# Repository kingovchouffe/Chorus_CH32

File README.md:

# Chorus_CH32
 Chorus effect based on ch32v003

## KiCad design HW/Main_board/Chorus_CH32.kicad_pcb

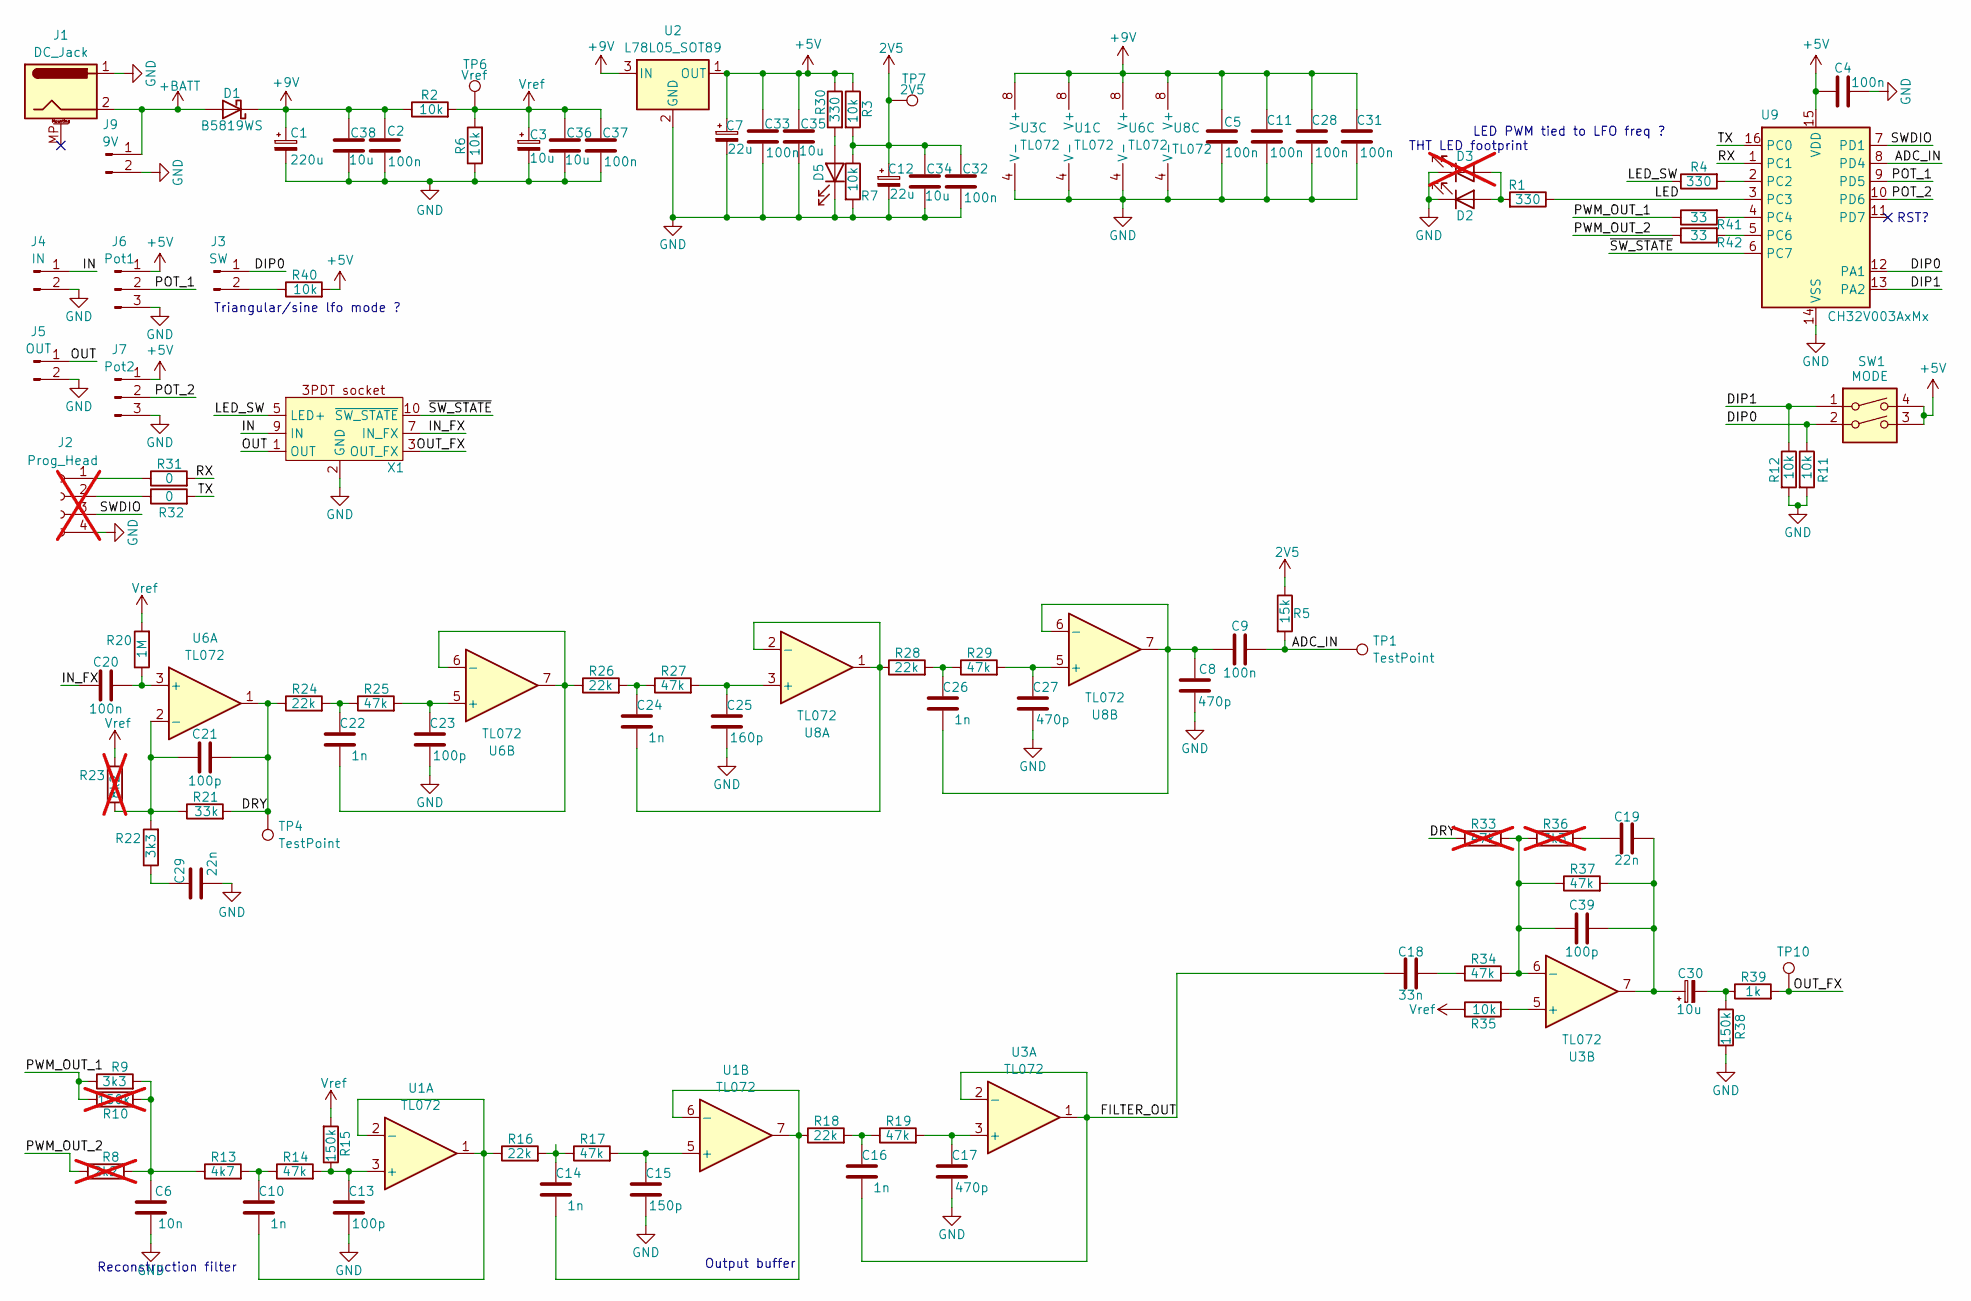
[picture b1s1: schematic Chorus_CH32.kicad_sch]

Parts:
C1: 220u; CP_Elec_6.3x7.7
C2, C4, C5, C9, C11, C20, C28, C31, C32, C33, C37: 100n; C_0603_1608Metric
C3: 10u; CP_Elec_5x5.4; lcsc C7171
C6: 10n; C_0603_1608Metric
C7, C12: 22u; CP_Elec_5x5.4; lcsc C7171
C8, C17, C27: 470p; C_0603_1608Metric
C10, C14, C16, C22, C24, C26: 1n; C_0603_1608Metric
C13, C21, C23, C39: 100p; C_0603_1608Metric
C15: 150p; C_0603_1608Metric
C18: 33n; C_0603_1608Metric
C19, C29: 22n; C_0603_1608Metric
C25: 160p; C_0603_1608Metric
C30: 10u; CP_Elec_5x5.4
C34, C35, C36, C38: 10u; C_0603_1608Metric
D1: B5819WS; D_SOD-323
D2, D5: CTL1; LED_0603_1608Metric
D3: CTL1; PinSocket_1x02_P1.27mm_Vertical; not fitted
J1: DC_Jack; BarrelJack_Horizontal
J2: Prog_Head; PinHeader_1x04_P1.27mm_Vertical; not fitted
J3: SW; PinHeader_1x02_P1.27mm_Vertical
J4: IN; PinHeader_1x02_P1.27mm_Vertical
J5: OUT; PinHeader_1x02_P1.27mm_Vertical
J6: Pot1; PinHeader_1x03_P1.27mm_Vertical
J7: Pot2; PinHeader_1x03_P1.27mm_Vertical
J9: 9V; PinHeader_1x02_P1.27mm_Vertical
R1, R4, R30: 330; R_0603_1608Metric
R2, R3, R6, R7, R11, R12, R35, R40: 10k; R_0603_1608Metric
R5: 15k; R_0603_1608Metric
R8: 2k2; R_0603_1608Metric; not fitted
R9, R22: 3k3; R_0603_1608Metric
R10: 150k; R_0603_1608Metric; not fitted
R13: 4k7; R_0603_1608Metric
R14, R17, R19, R25, R27, R29, R34, R37: 47k; R_0603_1608Metric
R15, R38: 150k; R_0603_1608Metric
R16, R18, R24, R26, R28: 22k; R_0603_1608Metric
R20: 1M; R_0603_1608Metric
R21: 33k; R_0603_1608Metric
R23: 8k2; R_0603_1608Metric; not fitted
R31, R32: 0; R_0603_1608Metric
R33: 47k; R_0603_1608Metric; not fitted
R36: 3k3; R_0603_1608Metric; not fitted
R39: 1k; R_0603_1608Metric
R41, R42: 33; R_0603_1608Metric
SW1: MODE; SW_DIP_SPSTx02_Slide_KingTek_DSHP02TS_W7.62mm_P1.27mm
TP1, TP4, TP10: TestPoint; TestPoint_Pad_D1.0mm
TP6: Vref; TestPoint_Pad_D1.0mm
TP7: 2V5; TestPoint_Pad_D1.0mm
U1, U3, U6, U8: TL072; SOIC-8_3.9x4.9mm_P1.27mm
U2: L78L05_SOT89; SOT-89-3
U9: CH32V003AxMx; SOP-16_3.9x9.9mm_P1.27mm
X1: PinHeader_1x10_P1.27mm_Vertical

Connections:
2V5: C12.1, C32.1, C34.1, R3.2, R5.1, R7.1, TP7.1
+5V: C4.1, C7.1, C33.1, C35.1, J6.1, J7.1, R3.1, R30.1, R40.2, SW1.3, SW1.4, U2.1 (OUT), U9.15 (VDD); also elsewhere on the board
+9V: C1.1, C2.1, C5.1, C11.1, C28.1, C31.1, C38.1, D1.1 (K), R2.1, U1.8 (V+), U2.3 (IN), U3.8 (V+), U6.8 (V+), U8.8 (V+)
+BATT: D1.2 (A), J1.2, J9.1
/ADC_IN: C9.2, R5.2, TP1.1, U9.8 (PD4)
/DIP0: J3.1, R11.1, SW1.2, U9.12 (PA1); also elsewhere on the board
/DIP1: R12.1, SW1.1, U9.13 (PA2); also elsewhere on the board
/DRY: C21.2, R21.2, R24.1, R33.1, TP4.1, U6.1
/FILTER_OUT: C16.2, C18.1, U3.1, U3.2 (-)
/IN: J4.1, X1.9 (IN)
/IN_FX: C20.1, X1.7 (IN_FX)
/LED: R1.1, U9.3 (PC3)
/LED_SW: R4.1, X1.5 (LED+)
/OUT: J5.1, X1.1 (OUT)
/OUT_FX: R39.2, TP10.1, X1.3 (OUT_FX)
/POT_1: J6.2, U9.9 (PD5); also elsewhere on the board
/POT_2: J7.2, U9.10 (PD6); also elsewhere on the board
/PWM_OUT_1: R9.1, R10.1, R41.1
/PWM_OUT_2: R8.1, R42.1
/RX: R31.2, U9.1 (PC1)
/SWDIO: J2.3, U9.7 (PD1); also elsewhere on the board
/TX: R32.2, U9.16 (PC0)
/~SW_STATE: U9.6 (PC7), X1.10 (~SW_STATE)
GND: C1.2, C2.2, C3.2, C4.2, C5.2, C6.2, C7.2, C8.2, C11.2, C12.2, C13.2, C15.2, C17.2, C23.2, C25.2, C27.2, C28.2, C29.2, C31.2, C32.2, C33.2, C34.2, C35.2, C36.2, C37.2, C38.2, D2.1 (K), D3.1 (K), D5.1 (K), J1.1, J2.4, J4.2, J5.2, J6.3, J7.3, J9.2, R6.1, R7.2, R11.2, R12.2, R38.1, U1.4 (V-), U2.2 (GND), U3.4 (V-), U6.4 (V-), U8.4 (V-), U9.14 (VSS), X1.2 (GND), X1.4 (GND), X1.6 (GND), X1.8 (GND); also elsewhere on the board
unnamed: C6.1, R8.2, R9.2, R10.2, R13.1
unnamed: C10.1, R13.2, R14.1
unnamed: C14.1, R16.2, R17.1
unnamed: C16.1, R18.2, R19.1
unnamed: C18.2, R34.1
unnamed: C19.1, R36.2
unnamed: C19.2, C30.1, C39.2, R37.2, U3.7
unnamed: C22.1, R24.2, R25.1
unnamed: C24.1, R26.2, R27.1
unnamed: C26.1, R28.2, R29.1
unnamed: C29.1, R22.1
unnamed: C30.2, R38.2, R39.1
unnamed: D2.2 (A), D3.2 (A), R1.2
unnamed: D5.2 (A), R30.2
unnamed 38: J2.1, R31.1; also elsewhere on the board
unnamed 39: J2.2, R32.1; also elsewhere on the board
unnamed: J3.2, R40.1
unnamed: C13.1, R14.2, R15.1, U1.3 (+)
unnamed: C10.2, R16.1, U1.1, U1.2 (-)
unnamed: C15.1, R17.2, U1.5 (+)
unnamed: C14.2, R18.1, U1.6 (-), U1.7
unnamed: C17.1, R19.2, U3.3 (+)
unnamed: R35.2, U3.5 (+)
unnamed: C39.1, R33.2, R34.2, R36.1, R37.1, U3.6 (-)
unnamed: C20.2, R20.1, U6.3 (+)
unnamed: C21.1, R21.1, R22.2, R23.1, U6.2 (-)
unnamed: C23.1, R25.2, U6.5 (+)
unnamed: C22.2, R26.1, U6.6 (-), U6.7
unnamed: C25.1, R27.2, U8.3 (+)
unnamed: C24.2, R28.1, U8.1, U8.2 (-)
unnamed: C27.1, R29.2, U8.5 (+)
unnamed: C8.1, C9.1, C26.2, U8.6 (-), U8.7
unnamed: R4.2, U9.2 (PC2)
unnamed: R41.2, U9.4 (PC4)
unnamed: R42.2, U9.5 (PC6)
Vref: C3.1, C36.1, C37.1, R2.2, R6.2, R15.2, R20.2, R23.2, R35.1, TP6.1

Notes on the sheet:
LED PWM tied to LFO freq ?
THT LED footprint
Triangular/sine lfo mode ?
RST?
Reconstruction filter
Output buffer

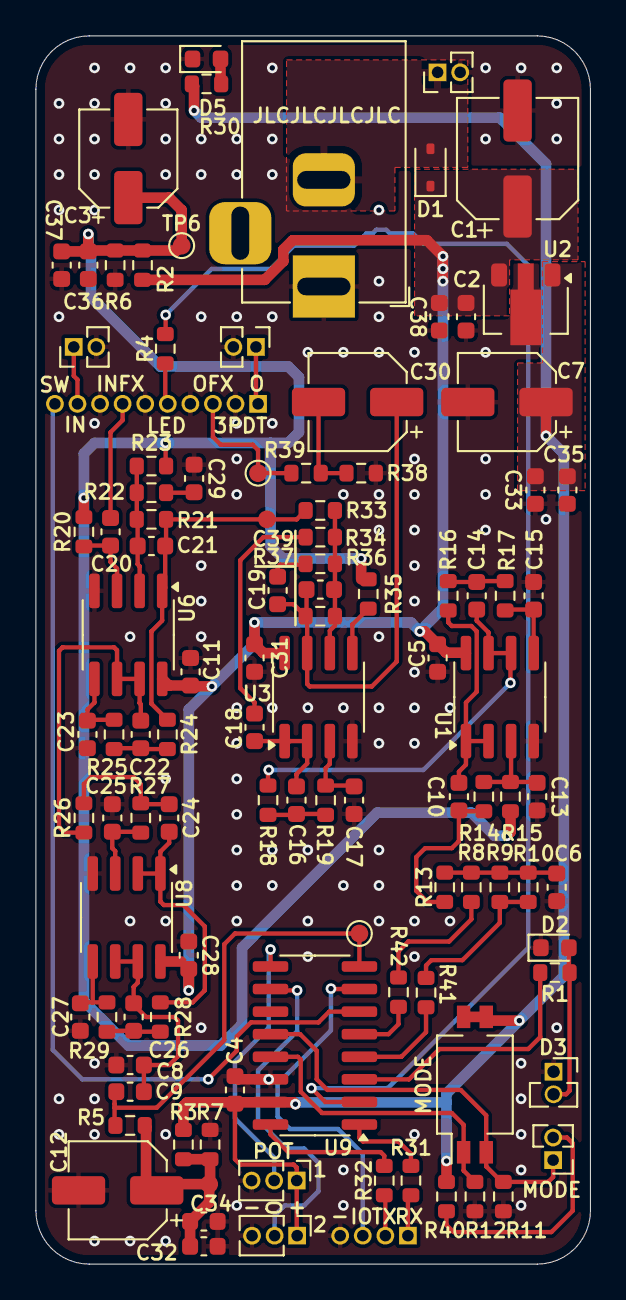
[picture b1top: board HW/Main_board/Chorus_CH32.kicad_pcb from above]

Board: 2 copper layers, 31.2 x 69.1 mm, 106 parts (0 on the bottom side), 60 nets.

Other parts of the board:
DEBUG: Prog_Head; PinHeader_1x04_P1.27mm_Vertical
MODE: MODE; SW_DIP_SPSTx02_Slide_KingTek_DSHP02TS_W7.62mm_P1.27mm
POT: Pot1; PinHeader_1x03_P1.27mm_Vertical
POT2: Pot2; PinHeader_1x03_P1.27mm_Vertical

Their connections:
+5V: MODE.3, MODE.4, POT.1, POT2.1; also elsewhere on the board
/DIP0: MODE.2; also elsewhere on the board
/DIP1: MODE.1; also elsewhere on the board
/POT_1: POT.2; also elsewhere on the board
/POT_2: POT2.2; also elsewhere on the board
/SWDIO: DEBUG.3; also elsewhere on the board
GND: DEBUG.4, POT.3, POT2.3; also elsewhere on the board
unnamed 38: DEBUG.1; also elsewhere on the board
unnamed 39: DEBUG.2; also elsewhere on the board

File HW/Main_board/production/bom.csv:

Designator,Footprint,Quantity,Value,LCSC Part #
C1,CP_Elec_6.3x7.7,1,220u,
"C10, C14, C16, C22, C24, C26",0603,6,1n,
"C11, C2, C20, C28, C31, C32, C33, C37, C4, C5, C9",0603,11,100n,
"C12, C7",CP_Elec_5x5.4,2,22u,
"C13, C21, C23, C39",0603,4,100p,
C15,0603,1,150p,
"C17, C27, C8",0603,3,470p,
C18,0603,1,33n,
"C19, C29",0603,2,22n,
C25,0603,1,160p,
"C3, C30",CP_Elec_5x5.4,2,10u,
"C34, C35, C36, C38",0603,4,10u,
C6,0603,1,10n,
D1,D_SOD-323,1,B5819WS,
"D2, D5",0603,2,CTL1,
J1,BarrelJack_Horizontal,1,DC_Jack,
J3,PinHeader_1x02_P1.27mm_Vertical,1,SW,
J4,PinHeader_1x02_P1.27mm_Vertical,1,IN,
J5,PinHeader_1x02_P1.27mm_Vertical,1,OUT,
J9,PinHeader_1x02_P1.27mm_Vertical,1,9V,
MODE,SW_DIP_SPSTx02_Slide_KingTek_DSHP02TS_W7.62mm_P1.27mm,1,MODE,
POT,PinHeader_1x03_P1.27mm_Vertical,1,Pot1,
POT2,PinHeader_1x03_P1.27mm_Vertical,1,Pot2,
"R1, R30, R4",0603,3,330,
"R11, R12, R2, R3, R35, R40, R6, R7",0603,8,10k,
R13,0603,1,4k7,
"R14, R17, R19, R25, R27, R29, R34, R37",0603,8,47k,
"R15, R38",0603,2,150k,
"R16, R18, R24, R26, R28",0603,5,22k,
R20,0603,1,1M,
R21,0603,1,33k,
"R22, R9",0603,2,3k3,
"R31, R32",0603,2,0,
R39,0603,1,1k,
"R41, R42",0603,2,33,
R5,0603,1,15k,
"TP1, TP10, TP4",TestPoint_Pad_D1.0mm,3,TestPoint,
TP6,TestPoint_Pad_D1.0mm,1,Vref,
TP7,TestPoint_Pad_D1.0mm,1,2V5,
"U1, U3, U6, U8",SOIC-8_3.9x4.9mm_P1.27mm,4,TL072,
U2,SOT-89-3,1,L78L05_SOT89,
U9,SOP-16_3.9x9.9mm_P1.27mm,1,CH32V003AxMx,
X1,PinHeader_1x10_P1.27mm_Vertical,1,~,

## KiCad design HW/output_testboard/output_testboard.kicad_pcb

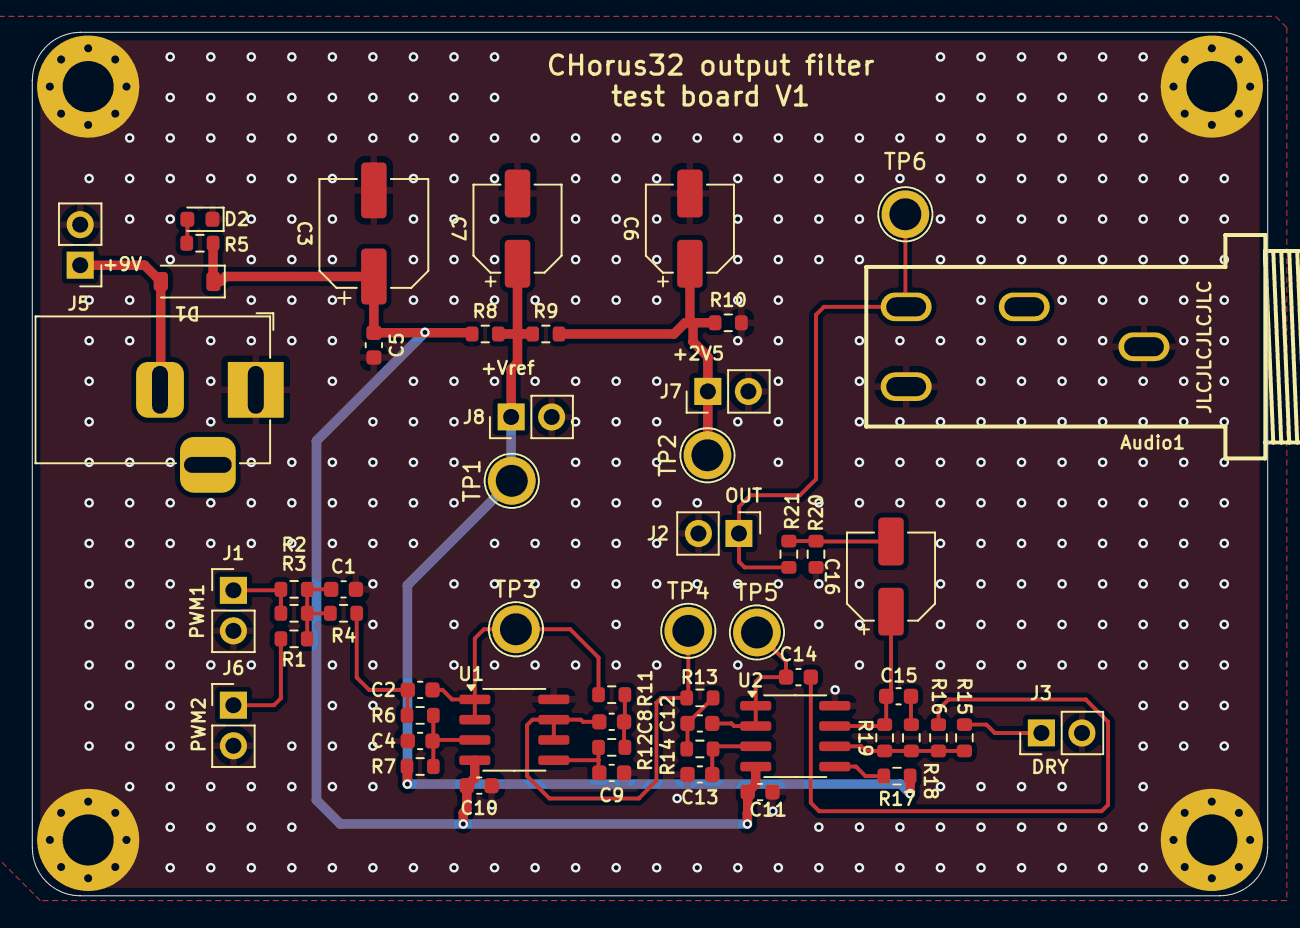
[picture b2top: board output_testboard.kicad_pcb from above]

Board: 2 copper layers, 77.4 x 54.1 mm, 60 parts (0 on the bottom side), 26 nets.

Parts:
Audio1: PJ-603A; AUDIO-TH_PJ-603A_1
C1: 15n; C_0603_1608Metric
C2, C8, C12: 1n; C_0603_1608Metric
C3: 100u; CP_Elec_6.3x7.7
C4: 100p; C_0603_1608Metric
C5, C10, C11: 100n; C_0603_1608Metric
C6, C7, C16: 10u; CP_Elec_5x5.4
C9: 160p; C_0603_1608Metric
C13: 470p; C_0603_1608Metric
C14: 33n; C_0603_1608Metric
C15: 22n; C_0603_1608Metric
D1: B5819WS; D_SOD-123
D2: LED; LED_0603_1608Metric
H1, H2, H3, H4: MountingHole_Pad; MountingHole_3.2mm_M3_Pad_Via
J1: IN1; PinHeader_1x02_P2.54mm_Vertical
J2, J3: OUT; PinHeader_1x02_P2.54mm_Vertical
J4: DC_Jack; BarrelJack_Horizontal
J5: 9V; PinHeader_1x02_P2.54mm_Vertical
J6: IN2; PinHeader_1x02_P2.54mm_Vertical
J7: 2V5; PinHeader_1x02_P2.54mm_Vertical
J8: Vref; PinHeader_1x02_P2.54mm_Vertical
R1: 2k2; R_0603_1608Metric
R2: 2M2; R_0603_1608Metric
R3, R7, R20: 150k; R_0603_1608Metric
R4: 4k7; R_0603_1608Metric
R5, R9, R17: 10k; R_0603_1608Metric
R6, R12, R14, R15, R16: 47k; R_0603_1608Metric
R8: 27k; R_0603_1608Metric
R10: 15k; R_0603_1608Metric
R11, R13: 22k; R_0603_1608Metric
R18: 3k3; R_0603_1608Metric
R19: 6k8; R_0603_1608Metric
R21: 1k; R_0603_1608Metric
TP1, TP2, TP3, TP4, TP5, TP6: TestPoint; TestPoint_Plated_Hole_D2.0mm
U1, U2: TL072; SOIC-8_3.9x4.9mm_P1.27mm

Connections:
2V5: C6.1, J7.1, R9.2, R10.1, TP2.1
+9V: C3.1, C5.1, C10.1, C11.1, D1.1 (K), R5.1, R8.1, U1.4 (V-), U2.4 (V-)
+BATT: D1.2 (A), J4.2, J5.1
/DRY: J3.1, R15.1
/FILTER_OUT: C12.2, C14.1, TP5.1, U2.1, U2.2 (-)
/OUT: Audio1.4, J2.1, R21.2, TP6.1
/PWM1_IN: J1.1, R2.1, R3.1
/PWM2_IN: J6.1, R1.1
GND: Audio1.2, Audio1.5, C1.2, C3.2, C4.2, C5.2, C6.2, C7.2, C9.2, C10.2, C11.2, C13.2, D2.1 (K), H1.1, H2.1, H3.1, H4.1, J1.2, J2.2, J3.2, J4.1, J5.2, J6.2, J7.2, J8.2, R10.2, R20.1, U1.8 (V+), U2.8 (V+)
unnamed: C1.1, R1.2, R2.2, R3.2, R4.1
unnamed: C2.1, R4.2, R6.1
unnamed: C8.1, R11.2, R12.1
unnamed: C12.1, R13.2, R14.1
unnamed: C14.2, R16.1
unnamed: C15.1, R18.2
unnamed: C15.2, C16.1, R19.2, U2.7
unnamed: C16.2, R20.2, R21.1
unnamed: D2.2 (A), R5.2
unnamed: C4.1, R6.2, R7.1, U1.3 (+)
unnamed: C2.2, R11.1, TP3.1, U1.1, U1.2 (-)
unnamed: C9.1, R12.2, U1.5 (+)
unnamed: C8.2, R13.1, TP4.1, U1.6 (-), U1.7
unnamed: C13.1, R14.2, U2.3 (+)
unnamed: R17.2, U2.5 (+)
unnamed: R15.2, R16.2, R18.1, R19.1, U2.6 (-)
Vref: C7.1, J8.1, R7.2, R8.2, R9.1, R17.1, TP1.1

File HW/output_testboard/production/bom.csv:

Designator,Footprint,Quantity,Value,LCSC Part #
Audio1,AUDIO-TH_PJ-603A_1,1,PJ-603A,C309273
C1,0603,1,15n,
"C10, C11, C5",0603,3,100n,
"C12, C2, C8",0603,3,1n,
C13,0603,1,470p,
C14,0603,1,33n,
C15,0603,1,22n,
C16,CP_Elec_5x5.4,1,10u,
C4,0603,1,100p,
C9,0603,1,160p,
D1,D_SOD-123,1,B5819WS,
D2,0603,1,LED,
J1,PinHeader_1x02_P2.54mm_Vertical,1,IN1,
"J2, J3",PinHeader_1x02_P2.54mm_Vertical,2,OUT,
J4,BarrelJack_Horizontal,1,DC_Jack,
J5,PinHeader_1x02_P2.54mm_Vertical,1,9V,
J6,PinHeader_1x02_P2.54mm_Vertical,1,IN2,
J7,PinHeader_1x02_P2.54mm_Vertical,1,2V5,
J8,PinHeader_1x02_P2.54mm_Vertical,1,Vref,
"R11, R13",0603,2,22k,
"R12, R14, R16, R6",0603,4,47k,
"R17, R5",0603,2,10k,
R18,0603,1,3k3,
R19,0603,1,6k8,
R2,0603,1,2M2,
"R20, R3, R7",0603,3,150k,
R21,0603,1,1k,
R4,0603,1,4k7,
"TP1, TP2, TP3, TP4, TP5, TP6",TestPoint_Plated_Hole_D2.0mm,6,TestPoint,
"U1, U2",SOIC-8_3.9x4.9mm_P1.27mm,2,TL072,

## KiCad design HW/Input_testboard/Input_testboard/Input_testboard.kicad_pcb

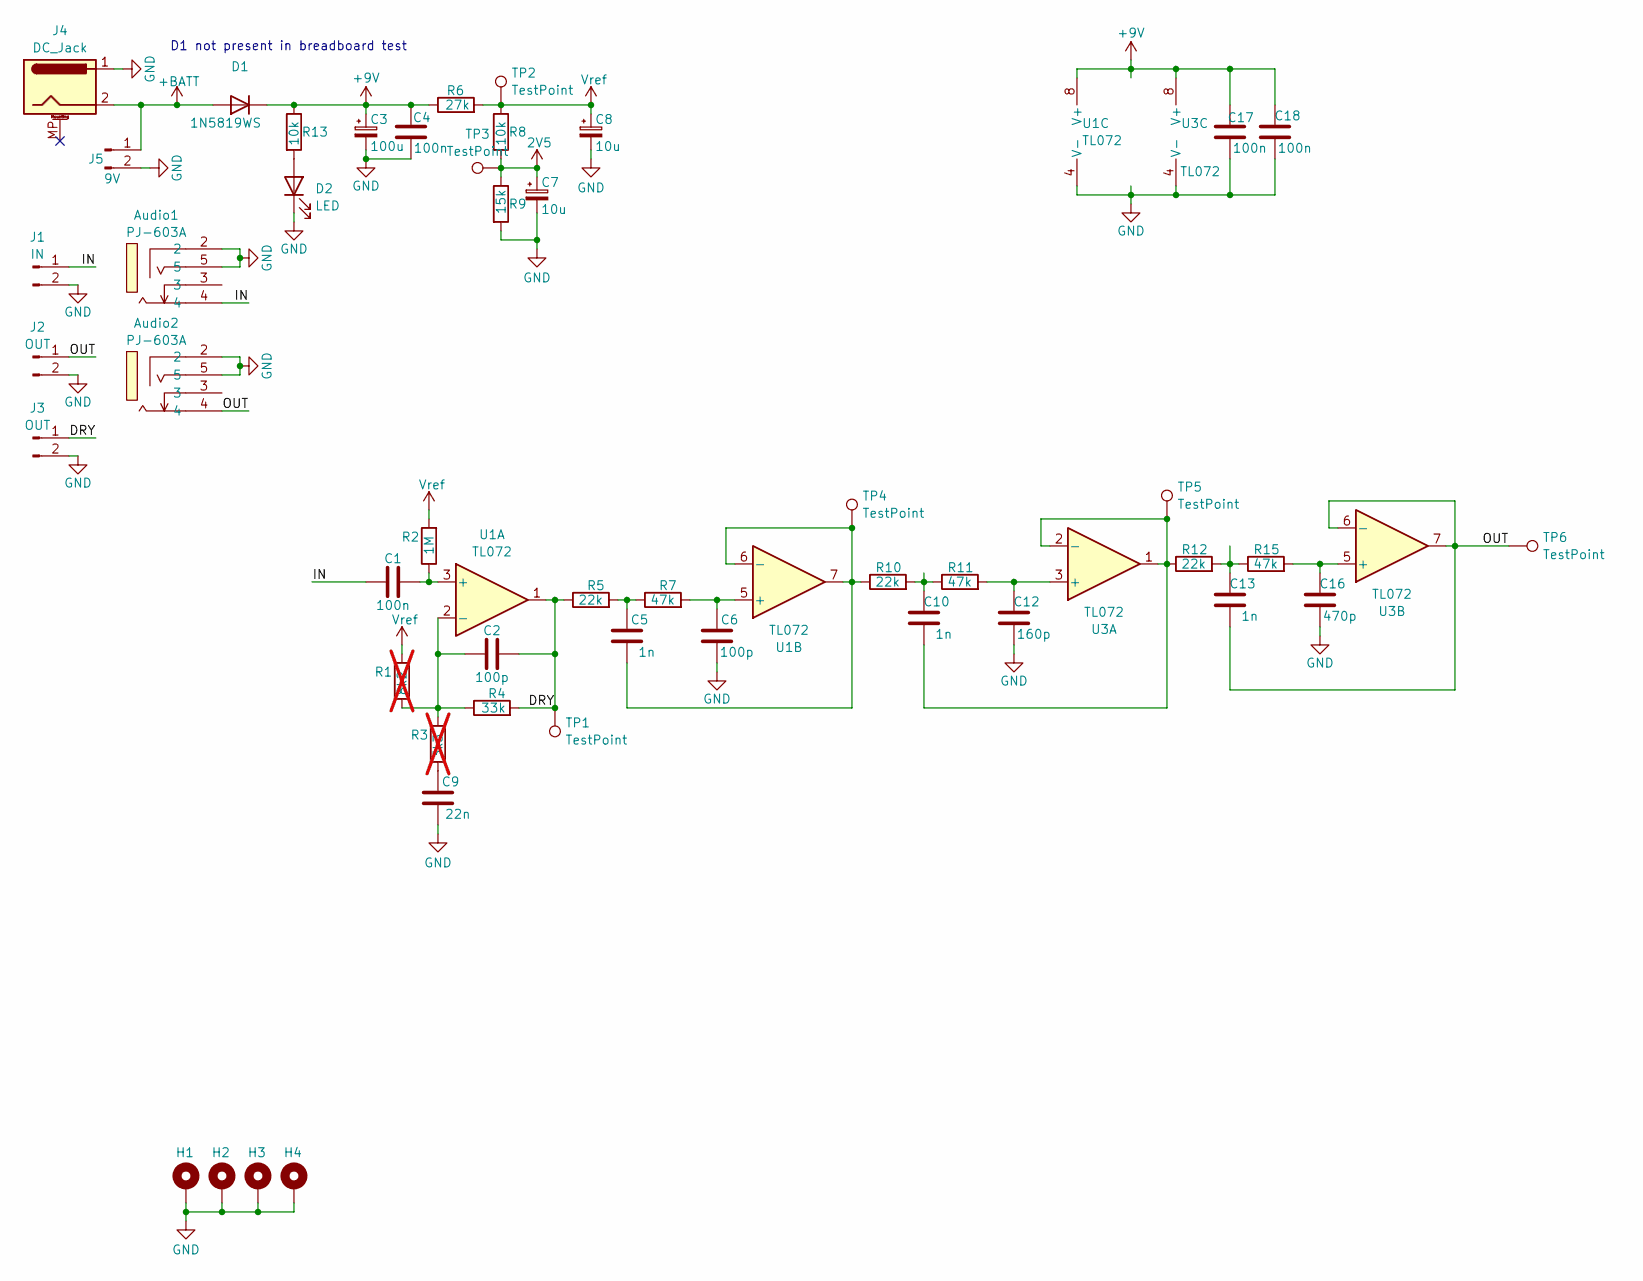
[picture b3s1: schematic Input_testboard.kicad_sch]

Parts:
Audio1, Audio2: PJ-603A; AUDIO-TH_PJ-603A_1; LCSC Part C309273
C1, C4, C17, C18: 100n; C_0603_1608Metric
C2, C6: 100p; C_0603_1608Metric
C3: 100u; CP_Elec_6.3x7.7
C5, C10, C13: 1n; C_0603_1608Metric
C7, C8: 10u; CP_Elec_5x5.4
C9: 22n; C_0603_1608Metric
C12: 160p; C_0603_1608Metric
C16: 470p; C_0603_1608Metric
D1: 1N5819WS; D_SOD-323
D2: LED; LED_0603_1608Metric
H1, H2, H3, H4: MountingHole_3.2mm_M3_Pad_Via
J1: IN; JST_PH_B2B-PH-K_1x02_P2.00mm_Vertical
J2, J3: OUT; JST_PH_B2B-PH-K_1x02_P2.00mm_Vertical
J4: DC_Jack; BarrelJack_Horizontal
J5: 9V; JST_PH_B2B-PH-K_1x02_P2.00mm_Vertical
R1: 8k2; R_0603_1608Metric; not fitted
R2: 1M; R_0603_1608Metric
R3: 3k3; R_0603_1608Metric; not fitted
R4: 33k; R_0603_1608Metric
R5, R10, R12: 22k; R_0603_1608Metric
R6: 27k; R_0603_1608Metric
R7, R11, R15: 47k; R_0603_1608Metric
R8, R13: 10k; R_0603_1608Metric
R9: 15k; R_0603_1608Metric
TP1, TP2, TP3, TP4, TP5, TP6: TestPoint; TestPoint_Pad_D1.0mm
U1, U3: TL072; SOIC-8_3.9x4.9mm_P1.27mm

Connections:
2V5: C7.1, R8.2, R9.1, TP3.1
+9V: C3.1, C4.1, C17.1, C18.1, D1.1 (K), R6.1, R13.1, U1.8 (V+), U3.8 (V+)
+BATT: D1.2 (A), J4.2, J5.1
/DRY: C2.2, J3.1, R4.2, R5.1, TP1.1, U1.1
/IN: Audio1.4, C1.1, J1.1
/OUT: Audio2.4, C13.2, J2.1, TP6.1, U3.6 (-), U3.7
GND: Audio1.2, Audio1.5, Audio2.2, Audio2.5, C3.2, C4.2, C6.2, C7.2, C8.2, C9.1, C9.2, C12.2, C16.2, C17.2, C18.2, D2.1 (K), H1.1, H2.1, H3.1, H4.1, J1.2, J2.2, J3.2, J4.1, J5.2, R3.1, R9.2, U1.4 (V-), U3.4 (V-)
unnamed: C5.1, R5.2, R7.1
unnamed: C10.1, R10.2, R11.1
unnamed: C13.1, R12.2, R15.1
unnamed: D2.2 (A), R13.2
unnamed: C1.2, R2.1, U1.3 (+)
unnamed: C2.1, R1.1, R3.2, R4.1, U1.2 (-)
unnamed: C6.1, R7.2, U1.5 (+)
unnamed: C5.2, R10.1, TP4.1, U1.6 (-), U1.7
unnamed: C12.1, R11.2, U3.3 (+)
unnamed: C10.2, R12.1, TP5.1, U3.1, U3.2 (-)
unnamed: C16.1, R15.2, U3.5 (+)
Vref: C8.1, R1.2, R2.2, R6.2, R8.1, TP2.1

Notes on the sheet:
D1 not present in breadboard test

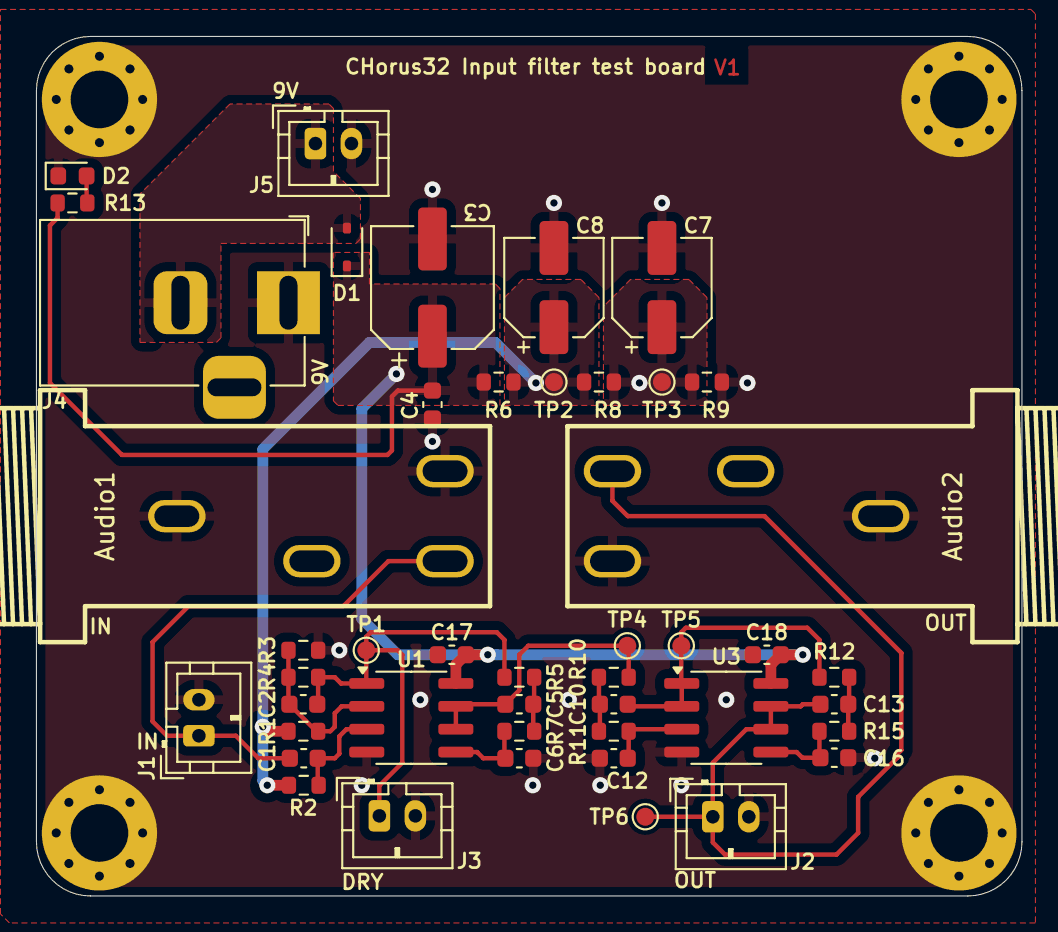
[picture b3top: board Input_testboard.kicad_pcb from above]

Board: 2 copper layers, 54.8 x 47.8 mm, 49 parts (0 on the bottom side), 19 nets.

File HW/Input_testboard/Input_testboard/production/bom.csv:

Designator,Footprint,Quantity,Value,LCSC Part #
"Audio1, Audio2",AUDIO-TH_PJ-603A_1,2,PJ-603A,C309273
"C1, C17, C18, C4",0603,4,100n,
"C10, C13, C5",0603,3,1n,
C12,0603,1,160p,
C16,0603,1,470p,
"C2, C6",0603,2,100p,
C3,CP_Elec_6.3x7.7,1,100u,
"C7, C8",CP_Elec_5x5.4,2,10u,
D1,D_SOD-323,1,1N5819WS,
D2,0603,1,LED,
J1,JST_PH_B2B-PH-K_1x02_P2.00mm_Vertical,1,IN,
"J2, J3",JST_PH_B2B-PH-K_1x02_P2.00mm_Vertical,2,OUT,
J4,BarrelJack_Horizontal,1,DC_Jack,
J5,JST_PH_B2B-PH-K_1x02_P2.00mm_Vertical,1,9V,
R1,0603,1,8k2,
"R10, R12, R5",0603,3,22k,
"R11, R15, R7",0603,3,47k,
"R13, R8",0603,2,10k,
R2,0603,1,1M,
R3,0603,1,3k3,
R4,0603,1,33k,
R6,0603,1,27k,
R9,0603,1,15k,
"TP1, TP2, TP3, TP4, TP5, TP6",TestPoint_Pad_D1.0mm,6,TestPoint,
"U1, U3",SOIC-8_3.9x4.9mm_P1.27mm,2,TL072,

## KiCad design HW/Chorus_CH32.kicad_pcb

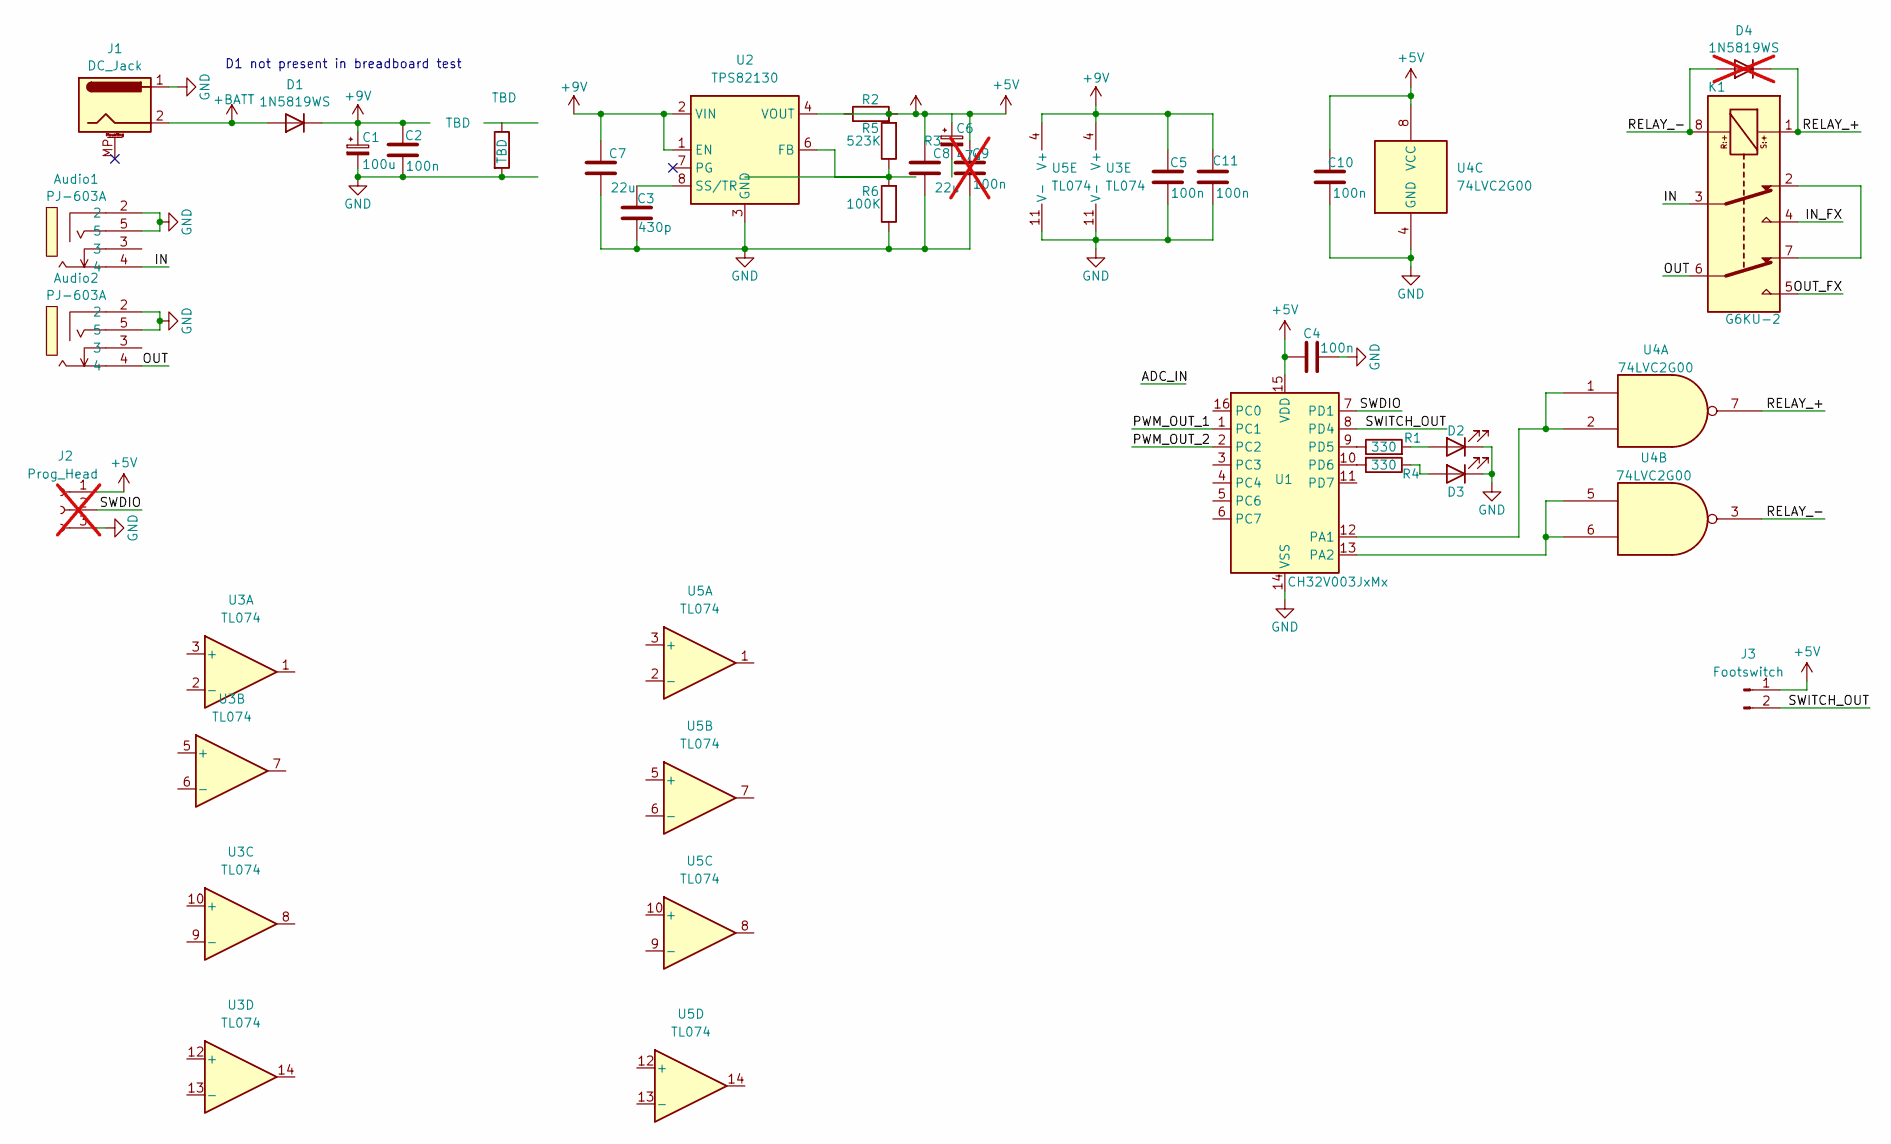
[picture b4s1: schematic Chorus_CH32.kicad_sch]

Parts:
Audio1, Audio2: PJ-603A; AUDIO-TH_PJ-603A; LCSC Part C309273
C1: 100u; CP_Elec_6.3x7.7
C2, C4, C5, C10, C11: 100n; C_0603_1608Metric
C3: 430p; C_0603_1608Metric
C6: 47u; CP_Elec_6.3x5.4
C7, C8: 22u; C_1210_3225Metric
C9: 100n; C_0603_1608Metric; not fitted
D1: 1N5819WS; D_SOD-323
D2: CTL1; LED_0603_1608Metric
D3: LED; LED_0603_1608Metric
D4: 1N5819WS; D_SOD-323; not fitted
J1: DC_Jack; BarrelJack_Horizontal
J2: Prog_Head; PinSocket_1x03_P1.27mm_Vertical; not fitted
J3: Footswitch; JST_PH_B2B-PH-K_1x02_P2.00mm_Vertical
K1: G6KU-2; Relay_DPDT_Omron_G6K-2F-Y
R1, R4: 330; R_0603_1608Metric
R2, R3: TBD; R_0603_1608Metric
R5: 523K; R_0603_1608Metric
R6: 100K; R_0603_1608Metric
U1: CH32V003JxMx; SOP-16_3.9x9.9mm_P1.27mm
U2: TPS82130; Texas_SIL0008D_MicroSiP-8-1EP_2.8x3mm_P0.65mm_EP1.1x1.9mm_T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
U3, U5: TL074; SOIC-14_3.9x8.7mm_P1.27mm
U4: 74LVC2G00; VSSOP-8_2.3x2mm_P0.5mm

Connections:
+5V: C4.1, C8.1, C9.1, C10.1, J2.1, J3.1, R5.2, U1.15 (VDD), U2.4 (VOUT), U2.5 (VOUT), U4.8 (VCC)
+9V: C1.1, C2.1, C5.1, C7.1, C11.1, D1.1 (K), R2.1, U2.1 (EN), U2.2 (VIN), U3.4 (V+), U5.4 (V+)
+BATT: D1.2 (A), J1.2
/IN: Audio1.4, K1.3
/IN_FX: K1.4
/OUT: Audio2.4, K1.6
/OUT_FX: K1.5
/PWM_OUT_1: U1.1 (PC1)
/PWM_OUT_2: U1.2 (PC2)
/RELAY_+: D4.1 (K), K1.1, U4.7
/RELAY_-: D4.2 (A), K1.8, U4.3
/SWDIO: J2.2, U1.7 (PD1)
/SWITCH_OUT: J3.2, U1.8 (PD4)
GND: Audio1.2, Audio1.5, Audio2.2, Audio2.5, C1.2, C2.2, C3.1, C4.2, C5.2, C6.2, C7.2, C8.2, C9.2, C10.2, C11.2, D2.1 (K), D3.1 (K), J1.1, J2.3, R3.2, R6.1, U1.14 (VSS), U2.3 (GND), U2.9 (GND), U3.11 (V-), U4.4 (GND), U5.11 (V-)
unnamed: D2.2 (A), R1.2
unnamed: D3.2 (A), R4.1
unnamed: K1.2, K1.7
unnamed: U1.12 (PA1), U4.1, U4.2
unnamed: U1.13 (PA2), U4.5, U4.6
unnamed: R1.1, U1.9 (PD5)
unnamed: R4.2, U1.10 (PD6)
unnamed: R5.1, R6.2, U2.6 (FB)
unnamed: C3.2, U2.8 (SS/TR)
TBD: C6.1, R2.2, R3.1

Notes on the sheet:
D1 not present in breadboard test

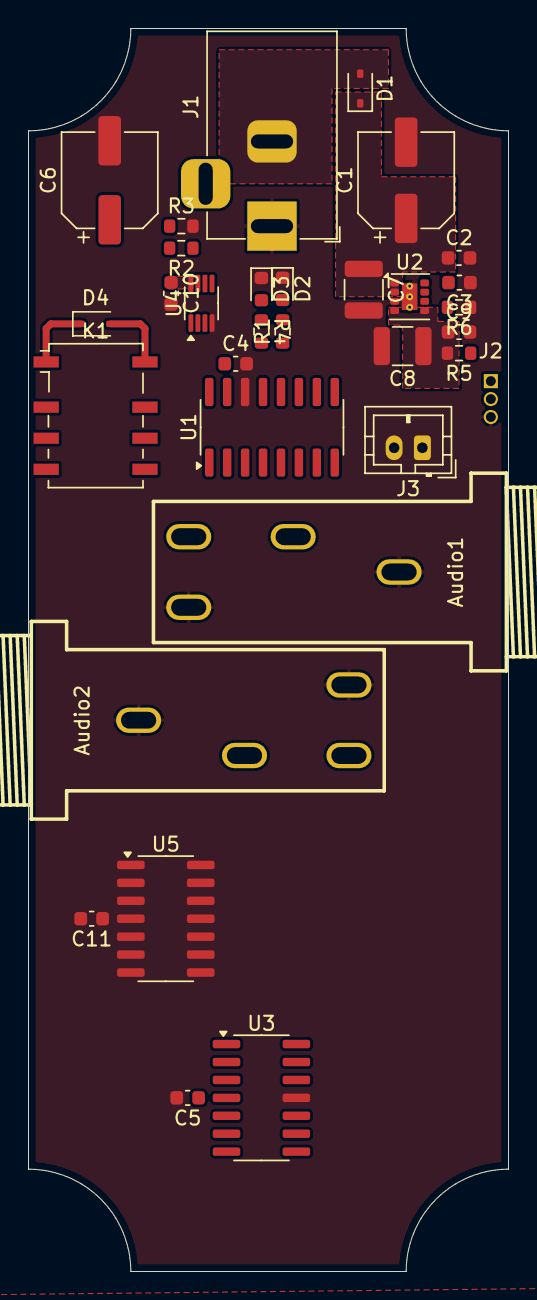
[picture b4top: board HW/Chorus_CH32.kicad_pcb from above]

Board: 4 copper layers, 34.0 x 88.1 mm, 32 parts (0 on the bottom side), 20 nets.

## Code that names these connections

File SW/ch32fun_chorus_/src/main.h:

#include "ch32fun.h"
#include <stdio.h>
#include <math.h>

#define InputPin PC4
#define RATE_POT gpio_ain
#define OutputPin PC0
#define PWM_CHANNEL 3
#define SAMPLE_RATE 97700
#define MAX_DELAY_MS 25   // Délai maximal en ms
#define LFO_FREQUENCY 0.5 // Fréquence du LFO en Hz
#define DEPTH_MS 10       // Profondeur de modulation en ms
#define TWO_PI 6.28318530718

#define BUFFER_LENGTH 256
volatile uint16_t buffer[BUFFER_LENGTH] = {0};
volatile uint16_t delay_buffer[BUFFER_LENGTH] = {0};
//void DMA1_Channel1_IRQHandler(void) __attribute__((interrupt));


void process_audio_dma(void)
{  
    static int sample_count = 0;
    // Lecture de l'ADC (valeur 12 bits)
    for (int i = 0; i < BUFFER_LENGTH; i++)
    {
        // Génération du LFO sinusoïdal
        
        float lfo_value = sinf(TWO_PI * LFO_FREQUENCY * sample_count / SAMPLE_RATE);
        sample_count++;

        // Calcul du retard dynamique
        int max_delay_samples = (SAMPLE_RATE * MAX_DELAY_MS) / 1000;
        int depth_samples = (SAMPLE_RATE * DEPTH_MS) / 1000;
        int delay_samples = max_delay_samples / 2 + (int)(depth_samples * lfo_value);
        int read_index = i - delay_samples;
        if (read_index < 0)
            read_index += BUFFER_LENGTH;

        // Sauvegarde du signal actuel dans le buffer circulaire
        delay_buffer[i] = buffer[read_index];
    }

}
// Instanciate dma copy to adc_buffer from adc HW
void init_dma_adc()
{
    // Start DMA clock
    RCC->AHBPCENR |= RCC_AHBPeriph_DMA1;

    // Setup DMA Channel 1 (adc triggered) as reading, 16-bit, linear buffer
    DMA1_Channel1->CFGR =
        DMA_CFGR1_MINC |                       // Incrémentation mémoire
        DMA_CFGR1_CIRC |                       // Mode circulaire
        DMA_CFGR1_PL_1 |                       // Priorité haute
        DMA_CFGR1_PSIZE_0 | DMA_CFGR1_MSIZE_0; // 16 bits

    // No of samples to get before irq
    DMA1_Channel1->CNTR = BUFFER_LENGTH;
    // Source
    DMA1_Channel1->PADDR = (uint32_t)&ADC1->RDATAR;
    // Destination
    DMA1_Channel1->MADDR = (uint32_t)buffer;
   
    // Enable IRQ and DMA channel
    NVIC_EnableIRQ(DMA1_Channel1_IRQn);
    DMA1_Channel1->CFGR |= DMA_IT_TC | DMA_CFGR1_EN;
    
}

// Instanciate dma copy to PWM register from adc buffer
void init_dma_copy_to_pwm()
{
    DMA1_Channel2->CFGR =
        DMA_CFGR2_MINC |                       // Incrémentation mémoire
        DMA_CFGR2_CIRC |                       // Mode circulaire
        DMA_CFGR2_PL_1 |                       // Priorité haute
        DMA_CFGR2_DIR |                        // memory to peripherals
        DMA_CFGR2_PSIZE_0 | DMA_CFGR2_MSIZE_0; // 16 bits
    // No of samples to get before irq
    DMA1_Channel2->CNTR = BUFFER_LENGTH;
    // Source
    DMA1_Channel2->MADDR = (uint32_t)delay_buffer;
    
    // Destination to PWM register
    DMA1_Channel2->PADDR = (uint32_t)&TIM2->CH3CVR;

    // Enable IRQ and DMA channel
    // DMA1_Channel2->CFGR |= DMA_CFGR1_TCIE;
    NVIC_EnableIRQ(DMA1_Channel2_IRQn);
    DMA1_Channel2->CFGR |= DMA_IT_TC | DMA_CFGR2_EN;
}
void init_timer2()
{
     // Enable TIM2
     RCC->APB1PCENR |= RCC_APB1Periph_TIM2;

     // using T2CH3 must also enable GPIOC
     RCC->APB2PCENR |= RCC_APB2Periph_GPIOC;
 
     // PC0 is T2CH3, 10MHz Output alt func, push-pull
     GPIOC->CFGLR &= ~(0xf << (4 * 0));
     GPIOC->CFGLR |= (GPIO_Speed_2MHz | GPIO_CNF_OUT_PP_AF) << (4 * 0);
 
     // Reset TIM2 to init all regs
     RCC->APB1PRSTR |= RCC_APB1Periph_TIM2;
     RCC->APB1PRSTR &= ~RCC_APB1Periph_TIM2;
 
     // SMCFGR: default clk input is CK_INT
     // set TIM2 clock prescaler divider
     TIM2->PSC = 0x000;
     // set PWM total cycle width
     TIM2->ATRLR = 500-1;
 
     TIM2->CHCTLR2 |= TIM_OC3M_2 | TIM_OC3M_1 | TIM_OC3PE;
 
     // CTLR1: default is up, events generated, edge align
     // enable auto-reload of preload
     TIM2->CTLR1 |= TIM_ARPE;
     TIM2->CTLR1 &= ~TIM_OPM;
 
     // Enable Channel outputs, set default state (based on TIM2_DEFAULT)
     TIM2->CCER |= TIM_CC3E | (TIM_CC3P & 0xff);
     // initialize counter
     TIM2->SWEVGR |= TIM_UG;
     //Enable DMA triggering
     TIM2->DMAINTENR |= TIM_TDE;
     TIM2->DMAINTENR |= TIM_UDE;
     //TIM2->CH3CVR =255;
}

void init_timer1()
{
    // TIMER
    // printf("Initializing timer...\r\n");
    RCC->APB2PCENR |= RCC_APB2Periph_TIM1;
    TIM1->CTLR1 |= TIM_CounterMode_Up | TIM_CKD_DIV1;
    TIM1->CTLR2 = TIM_MMS_1;
    TIM1->ATRLR = 500 - 1; // Foutput=(48MHz)/(PSC-1)(ARR+1)
    TIM1->PSC = 0;
    //TIM1->RPTCR = 0;
    //TIM1->SWEVGR = TIM_PSCReloadMode_Immediate;
    NVIC_EnableIRQ(TIM1_UP_IRQn);
    TIM1->INTFR = ~TIM_FLAG_Update;
    //TIM1->DMAINTENR |= TIM_IT_Update;
    TIM1->BDTR |= TIM_MOE;
    TIM1->DMAINTENR |= TIM_TDE;
    TIM1->DMAINTENR = TIM_UDE;

    init_timer2();
    // Enable TIM
    TIM2->CTLR1 |= TIM_CEN;
    TIM1->CTLR1 |= TIM_CEN;
}

void init_adc()
{
    // to be changed to PD4 for the input PD5 for rate pot and PD6 for the depth
    RCC->APB2PCENR |= RCC_APB2Periph_GPIOC;
    GPIOC->CFGLR &= ~(0xf << (4 * 4)); // CNF = 00: Analog, MODE = 00: Input

    RCC->APB2PCENR |= RCC_APB2Periph_ADC1;

    // Reset the ADC to init all regs
    RCC->APB2PRSTR |= RCC_APB2Periph_ADC1;
    RCC->APB2PRSTR &= ~RCC_APB2Periph_ADC1;

    // ADCCLK = 24 MHz => RCC_ADCPRE divide by 2
    RCC->CFGR0 &= ~RCC_ADCPRE;     // Clear out the bis in case they were set
    RCC->CFGR0 |= RCC_ADCPRE_DIV2; // set it to 010xx for /2.

    // Keep CALVOL register with initial value
    ADC1->CTLR2 = ADC_ADON | ADC_DMA | ADC_EXTTRIG | ADC_ExternalTrigConv_T1_TRGO;

    // Possible times: 0->3,1->9,2->15,3->30,4->43,5->57,6->73,7->241 cycles
    ADC1->SAMPTR2 = 7 /*3 cycles*/ << (3 /*offset per channel*/ * 1 /*channel*/);

    // Set sequencer to channel 2 only
    ADC1->RSQR3 = 2;

    // Calibrate
    ADC1->CTLR2 |= ADC_RSTCAL;
    while (ADC1->CTLR2 & ADC_RSTCAL)
        ;

    ADC1->CTLR2 |= ADC_CAL;
    while (ADC1->CTLR2 & ADC_CAL)
        ;

    ADC1->RDATAR; // wake up the dma
}
void DMA1_Channel1_IRQHandler(void) __attribute__((interrupt));
void DMA1_Channel1_IRQHandler()
{       printf("coucou\r\n");
        // DMA complete ?
        if (DMA1->INTFR & DMA1_FLAG_TC1) {
            DMA1->INTFCR = DMA_CTCIF1;
            process_audio_dma(); 
            // rearmed dma
            init_dma_adc();
        }
}

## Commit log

2024-09-21 add documentation and simulation
2024-09-21 add different simulation
    Input buffering and AA filter
2024-11-29 pre-schematic + pre-layout
2025-02-11 lots of things
    Add Datasheet of ch32v003
    Change of the input filter (tested)
    change of simulation schem
    New SW repo using ch32v003fun for better perf and memory usage
    Working ADC to PWM but no sound (output filter)
2025-03-13 working passthrough code with dma + ouput buffer HW
2025-03-22 add gitignore
2025-03-22 update output buffer sim
2025-03-22 correction on output board and new main layout/schem
2025-03-22 move driver function to main.h
2025-03-22 remove kicad autosave repo
2025-03-22 improved PSU filtering
2025-03-22 silkscreen ok
2025-03-22 moved spdt connector
2025-03-24 main board sent to fab
2025-03-24 added chorus process trigered by dma intr not working
2025-03-25 remove header change config of debugger
